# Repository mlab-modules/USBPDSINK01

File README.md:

# USBPDSINK01 - USB Power Delivery sink controller

The [MLAB](https://www.mlab.cz) module [USBPDSINK01](https://www.mlab.cz/module/USBPDSINK01) is a powerful module containing the [STUSB4500](https://www.st.com/en/interfaces-and-transceivers/stusb4500.html) [power-delivery sink controller](https://en.wikipedia.org/wiki/USB_hardware#USB_Power_Delivery). The module is designed to provide a flexible and reliable solution for various applications requiring USB power delivery PD2 and PD3 protocols. 

## Specifications

[STUSB4500](https://www.st.com/en/interfaces-and-transceivers/stusb4500.html) is a USB-C PD controller for Power Sinks / UFP (on the device side). It is certified by the USB-IF consortium for [USB Type-C](https://www.usb.org/usb-type-c) and [USB Power Delivery](https://www.usb.org/usb-charger-pd) applications (USB-C & USB PD).

### Module Features

- **USB-C Input:** The module accepts power through the USB-C connector.
- **Power Output:** The output is led to a pin header and also to a WAGO terminal block to high-power tool-free connection of powered devices.
- **Indicator Pins with LED:** Some status pins contain LEDs, and these signals are connected to the pin header.
- **Pull-up Resistors:** The module has pull-up resistors on the output signals for fast implementation into your system. PullUp voltage can be attached to header pins or can be used internal 3v3.
- **Integrated LDO:** The module is equipped with an integrated LDO for powering pullups and LED (no output).
- **External Power Supply:** The VSYS power can also be attached externally.
- **Communication via I2C:** The module communicates via I2C bus.
- **Key Features of [STUSB4500](https://www.st.com/en/interfaces-and-transceivers/stusb4500.html):**
  - Auto-run USB Type-C™ and USB PD sink controller handling and detection
  - Dead battery mode support
  - Up to 3 configurable sink PDO profiles (with permanent memory)
  - Integrated VBUS switching gates (PMOS transistor)
  - Integrated VBUS voltage monitoring
  - Internal and/or external VBUS discharge paths (for high capacitance networks)
  - Short-circuit protection on VBUS pins (22 V)
  - High-voltage capability on VBUS pins (28 V)
  - Dual power supply (VSYS and/or VDD): VDD = [4.1 V; 22 V] or VSYS = [3.0 V; 5.5 V]
  - Accessory mode support
  - Temperature range: -40 °C to 105 °C
  - ESD: 3 kV HBM - 1.5 kV CDM
  - Certified: USB Type-C™ rev 1.2, USB PD rev 2.0 (Official Test ID: TID #1000133)
  - Interoperable with USB PD rev 3.0

### Pinout and Their Meaning

- **ALERT:** Notification of various states and events.
- **USB-C orientation:** Indication of the connected side of the USB-C cable.
- **CONNECTED:** Cable connection indication.
- **GPIO:** General input/output pin, configurable for various purposes.
- **OK2 & OK3:** Pins that are active when the corresponding PDO is selected. Can indicate the selected voltage.
- **RESET:** Pin for resetting the USB-PD controller.

## Possible Applications
The MLAB module USBPDSINK01 is ideal for a wide range of applications, including:

- **Device Charging:** Fast and efficient charging of devices with high battery capacity. The module allows automatic negotiation of higher voltage from the source (>5V) up to 100W (20V@5A), ensuring the optimal charging profile for various types of batteries.

- **Scientific and Industrial Applications:** Flexible power and control for various scientific and industrial applications. With the ability to configure up to three sink PDO profiles, the module can be tailored to specific research or experiment needs.

- **Development and Testing:** The module can be used as part of development and testing stations for various products. With integrated VBUS switching gates and short-circuit protection up to 22 V, the module offers a robust and safe solution for testing and tuning.

- **Universal Power Source:** The module can serve as a universal power source for various devices, including charges, speakers, machines, or other electronic devices that require high-wattage power sources.

## Schematics

## Documentation
- [STUSB4500 Datasheet](https://www.st.com/resource/en/datasheet/stusb4500.pdf)

## Conclusion

The MLAB module USBPDSINK01 represents a robust and flexible solution for various applications requiring USB power delivery. With the integrated STUSB4500 controller, advanced features, and a wide range of possible applications, this module is the ideal choice for developers and engineers looking for a reliable and powerful solution.

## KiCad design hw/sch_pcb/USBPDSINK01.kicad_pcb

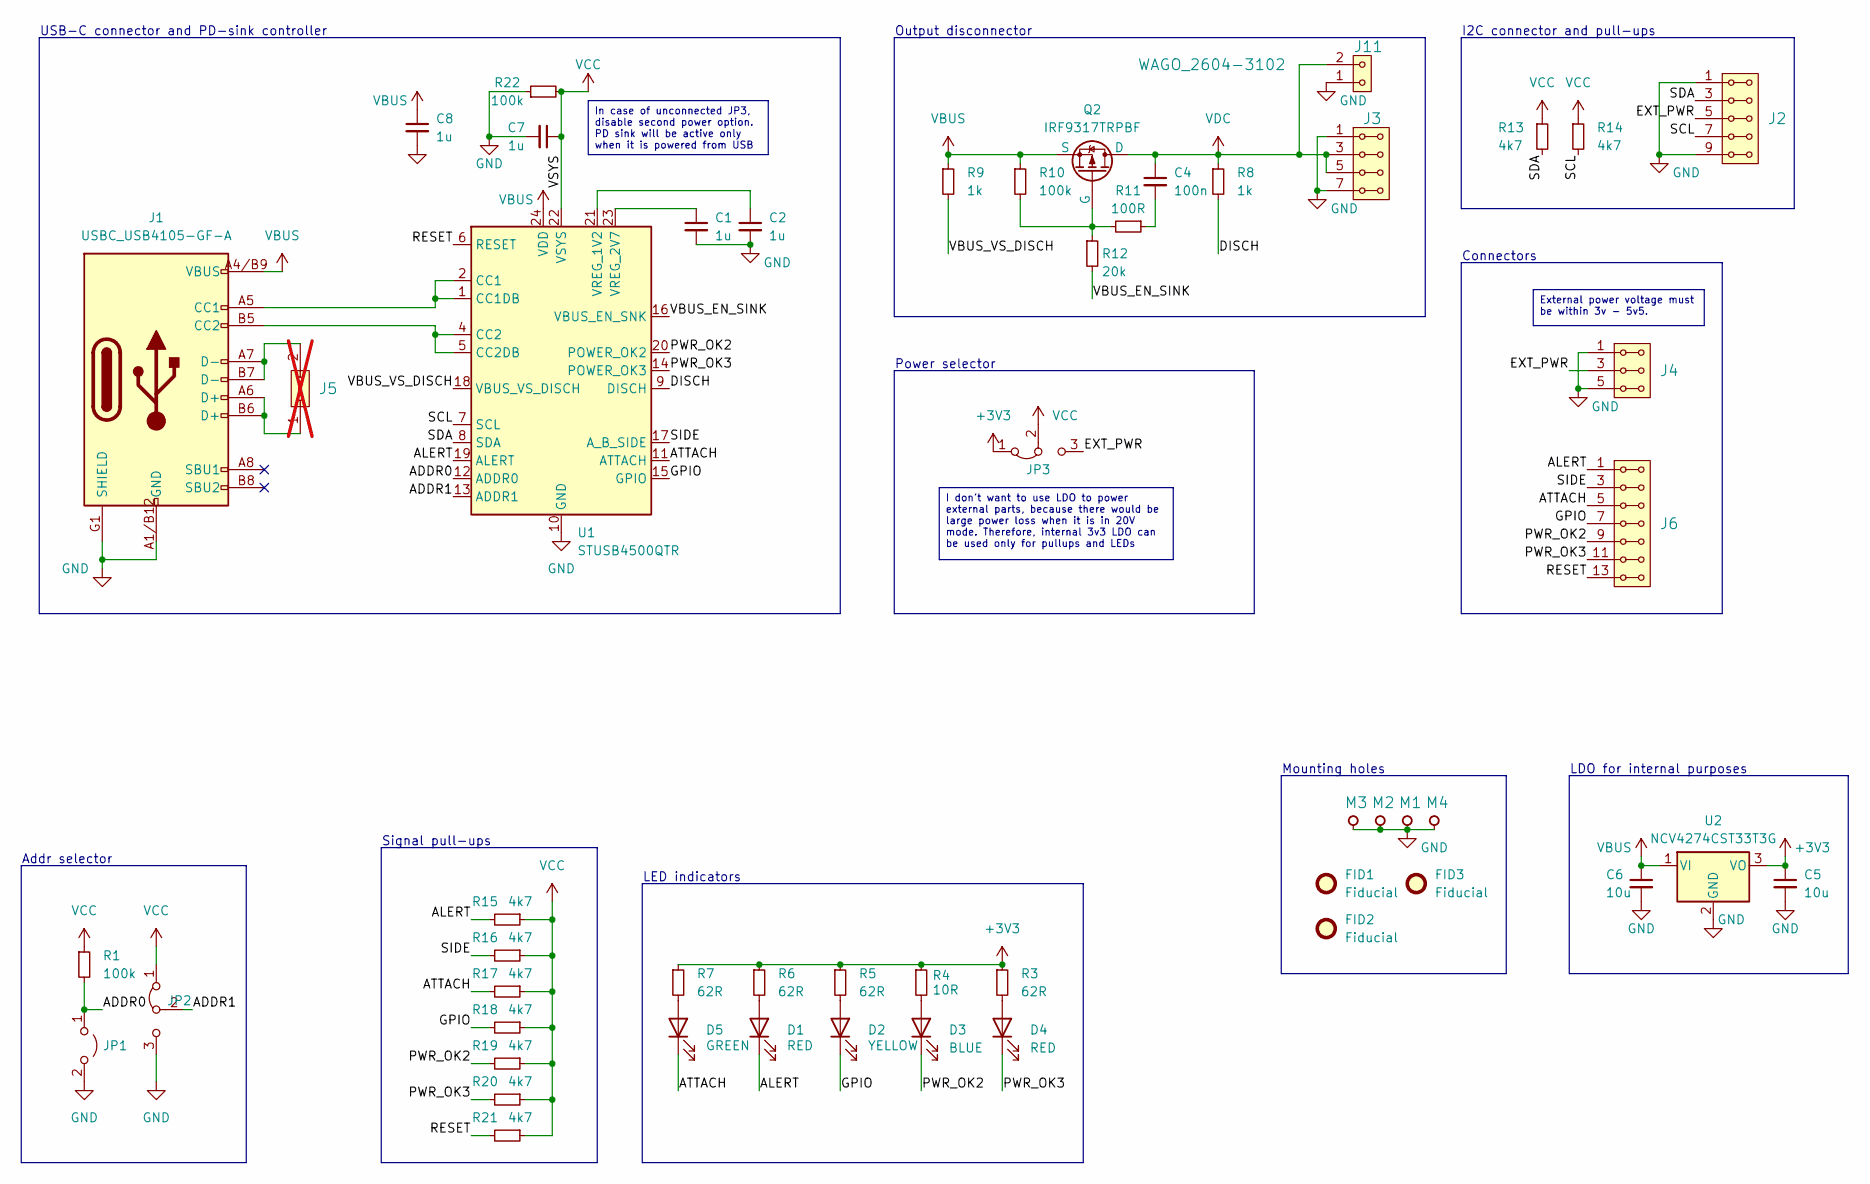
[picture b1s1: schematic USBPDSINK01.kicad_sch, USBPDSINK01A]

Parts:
C1, C2, C7, C8: 1u; C_0805_2012Metric; MPN C0805 1u
C4: 100n; C_0805_2012Metric; MPN C0805 100n
C5, C6: 10u; C_0805_2012Metric; MPN C0805 10u
D1, D4: RED; LED_1206_mill; MPN KPTR-3216SURCK
D2: YELLOW; LED_1206_mill; MPN KPTR-3216SYCK
D3: BLUE; LED_1206_mill; MPN KPTR-3216QBC-D
D5: GREEN; LED_1206_mill; MPN KPTR-3216CGCK
FID1, FID2, FID3: Fiducial; Fiducial_1mm_Mask2mm
J1: USBC_USB4105-GF-A; USBC GCT_USB4105-GF-A; MPN USB4105-GF-A
J2: HEADER_2x05_PARALLEL; PinHeader_2x05_P2.54mm_Vertical
J3: HEADER_2x04_PARALLEL; PinHeader_2x04_P2.54mm_Vertical
J4: HEADER_2x03_PARALLEL; PinHeader_2x03_P2.54mm_Vertical
J5: HEADER_2x01; PinHeader_2x01_P2.54mm_Vertical; not fitted
J6: HEADER_2x07_PARALLEL; PinHeader_2x07_P2.54mm_Vertical
J11: WAGO_2604-3102; TerminalBlock_WAGO_2604-3102_1x02_P5.00mm_Vertical; MPN 2604-3102
JP1: Jumper_2_Open; PinHeader_2x01_P2.54mm_Vertical
JP2: Jumper_3_Bridged12; SolderJumper-3_P1.3mm_Bridged12_RoundedPad1.0x1.5mm
JP3: Jumper_3_Bridged12; PinHeader_1x03_P2.54mm_Vertical
M1, M2, M3, M4: HOLE; MountingHole_3mm
Q2: IRF9317TRPBF; SOIC-8_3.9x4.9mm_P1.27mm; MPN IRF9317TRPBF
R1, R10, R22: 100k; R_0805_2012Metric; MPN R0805 100K 1%
R3, R5, R6, R7: 62R; R_0805_2012Metric; MPN R0805 62R 1%
R4: 10R; R_0805_2012Metric; MPN R0805 10R 1%
R8, R9: 1k; R_0805_2012Metric; MPN R0805 1k 1%
R11: 100R; R_0805_2012Metric; MPN R0805 100R 1%
R12: 20k; R_0805_2012Metric; MPN R0805 20k 1%
R13, R14, R15, R16, R17, R18, R19, R20, R21: 4k7; R_0805_2012Metric; MPN R0805 4k7 1%
U1: STUSB4500QTR; QFN-24-1EP_4x4mm_P0.5mm_EP2.7x2.7mm; MPN STUSB4500QTR
U2: NCV4274CST33T3G; SOT-223-3_TabPin2; MPN NCV4274CST33T3G

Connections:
+3V3: C5.1, JP3.1 (A), R3.1, R4.1, R5.1, R6.1, R7.1, U2.3 (VO)
/ADDR0: JP1.1 (A), R1.2, U1.12 (ADDR0)
/ADDR1: JP2.2 (C), U1.13 (ADDR1)
/ALERT: D1.1 (K), J6.1, J6.2, R15.2, U1.19 (ALERT)
/ATTACH: D5.1 (K), J6.5, J6.6, R17.2, U1.11 (ATTACH)
/DISCH: R8.2, U1.9 (DISCH)
/EXT_PWR: J2.5, J2.6, J4.3, J4.4, JP3.3 (B)
/GPIO: D2.1 (K), J6.7, J6.8, R18.2, U1.15 (GPIO)
/PWR_OK2: D3.1 (K), J6.9, J6.10, R19.2, U1.20 (POWER_OK2)
/PWR_OK3: D4.1 (K), J6.11, J6.12, R20.2, U1.14 (POWER_OK3)
/RESET: J6.13, J6.14, R21.2, U1.6 (RESET)
/SCL: J2.7, J2.8, R14.2, U1.7 (SCL)
/SDA: J2.3, J2.4, R13.2, U1.8 (SDA)
/SIDE: J6.3, J6.4, R16.2, U1.17 (A_B_SIDE)
/VBUS_EN_SINK: R12.2, U1.16 (VBUS_EN_SNK)
/VBUS_VS_DISCH: R9.2, U1.18 (VBUS_VS_DISCH)
GND: C1.2, C2.2, C5.2, C6.2, C7.2, C8.2, J1.A1/B12 (GND), J1.B1/A12 (GND), J1.G1 (SHIELD), J1.G2 (SHIELD), J1.G3 (SHIELD), J1.G4 (SHIELD), J2.1, J2.2, J2.9, J2.10, J3.1, J3.2, J3.7, J3.8, J4.1, J4.2, J4.5, J4.6, JP1.2 (B), JP2.3 (B), M1.1, M2.1, M3.1, M4.1, R22.1, U1.10 (GND), U1.25 (GND), U2.2 (GND); also elsewhere on the board
unnamed: C4.2, R11.1
unnamed: D1.2 (A), R6.2
unnamed: D2.2 (A), R5.2
unnamed: D3.2 (A), R4.2
unnamed: D4.2 (A), R3.2
unnamed: D5.2 (A), R7.2
unnamed: J1.A5 (CC1), U1.1 (CC1DB), U1.2 (CC1)
unnamed: J1.B5 (CC2), U1.4 (CC2), U1.5 (CC2DB)
unnamed: J1.A6 (D+), J1.B6 (D+), J5.1
unnamed: J1.A7 (D-), J1.B7 (D-), J5.2
unnamed: Q2.4 (G), R10.2, R11.2, R12.1
unnamed: C2.1, U1.21 (VREG_1V2)
unnamed: C1.1, U1.23 (VREG_2V7)
VBUS: C6.1, C8.1, J1.A4/B9 (VBUS), J1.B4/A9 (VBUS), Q2.1 (S), Q2.2 (S), Q2.3 (S), R9.1, R10.1, U1.24 (VDD), U2.1 (VI)
VCC: C7.1, JP2.1 (A), JP3.2 (C), R1.1, R13.1, R14.1, R15.1, R16.1, R17.1, R18.1, R19.1, R20.1, R21.1, R22.2, U1.22 (VSYS)
VDC: C4.1, J3.3, J3.4, J3.5, J3.6, Q2.5 (D), Q2.6 (D), Q2.7 (D), Q2.8 (D), R8.1; also elsewhere on the board

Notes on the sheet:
I don't want to use LDO to power external parts, because there would be large power loss when it is in 20V mode. Therefore, internal 3v3 LDO can be used only for pullups and LEDs
External power voltage must be within 3v - 5v5.
In case of unconnected JP3, disable second power option. PD sink will be active only when it is powered from USB
Power selector
USB-C connector and PD-sink controller
Addr selector
Mounting holes
I2C connector and pull-ups
Signal pull-ups
Connectors
LED indicators
LDO for internal purposes
Output disconnector

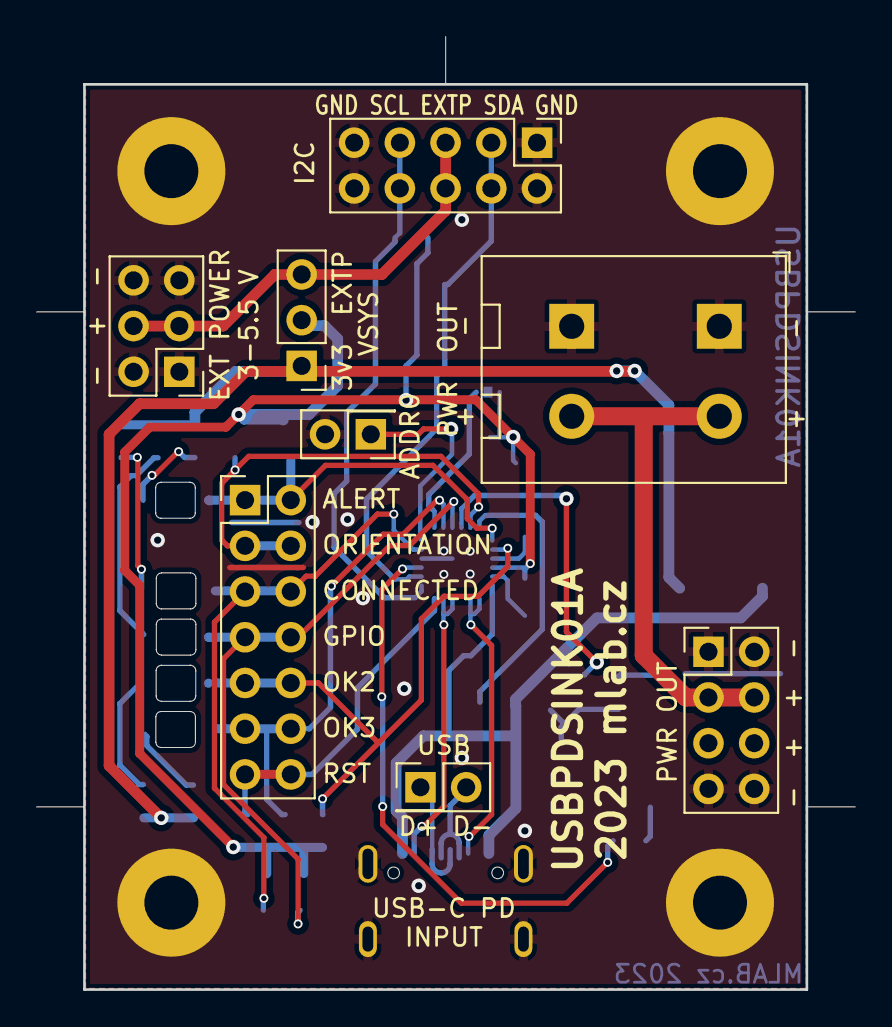
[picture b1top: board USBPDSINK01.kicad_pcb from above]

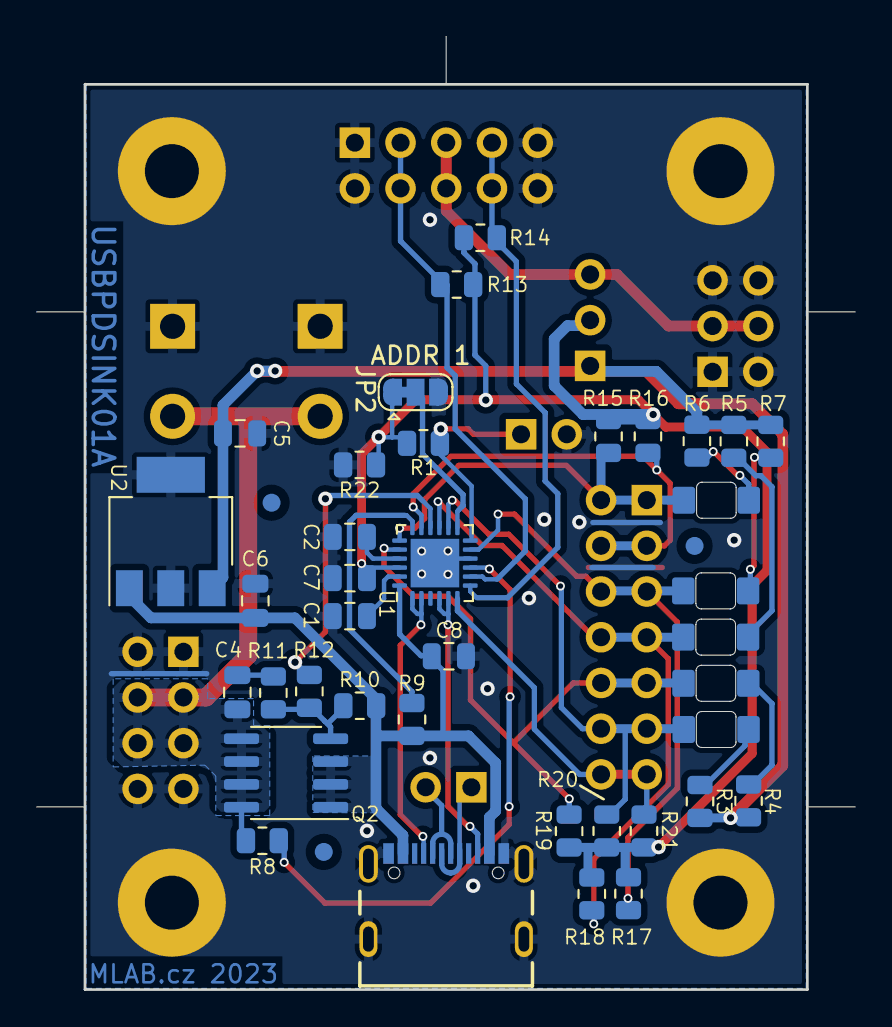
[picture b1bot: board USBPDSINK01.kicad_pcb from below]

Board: 2 copper layers, 45.4 x 52.9 mm, 53 parts (41 on the bottom side), 33 nets.

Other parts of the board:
J7: WAGO_2604-3102; TerminalBlock_WAGO_2604-3102_1x02_P5.00mm_Vertical

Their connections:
GND: J7.1; also elsewhere on the board
VDC: J7.2; also elsewhere on the board

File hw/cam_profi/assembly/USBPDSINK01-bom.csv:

Component,Description,Part,References,Value,Footprint,Quantity Per PCB,Datasheet,mfpn,mpn,ust_id,sim.pins,sim.type
1,"Unpolarized capacitor, small symbol",C_Small,C4,100n,C_0805_2012Metric,1,~,C0805 100n,C0805 100n,5c70984712875079b91f8b4c,,
2,"Unpolarized capacitor, small symbol",C_Small,C1C2C7C8,1u,C_0805_2012Metric,4,~,C0805 1u,C0805 1u,5c70984712875079b91f8b50,,
3,"Unpolarized capacitor, small symbol",C_Small,C5C6,10u,C_0805_2012Metric,2,~,C0805 10u,C0805 10u,5c70984712875079b91f8b53,,
4,Light emitting diode,LED,D3,BLUE,LED_1206_mill,1,~,KPTR-3216QBC-D,KPTR-3216QBC-D,650b4b9e462c6d9e7205459d,,
5,Light emitting diode,LED,D5,GREEN,LED_1206_mill,1,~,KPTR-3216CGCK,KPTR-3216CGCK,64ab2ec176c82a1d3b57875b,,
6,Light emitting diode,LED,D1D4,RED,LED_1206_mill,2,~,KPTR-3216SURCK,KPTR-3216SURCK,64ab2fba76c82a1d3b57877d,,
7,Light emitting diode,LED,D2,YELLOW,LED_1206_mill,1,~,KPTR-3216SYCK,KPTR-3216SYCK,650b4b13462c6d9e7205456a,,
8,"2x03 2.54 mm pitch header, 2 pins next to each other are connected",HEADER_2x03_PARALLEL,J4,HEADER_2x03_PARALLEL,PinHeader_2x03_P2.54mm_Vertical,1,,,,,,
9,"2x04 2.54 mm pitch header, 2 pins next to each other are connected",HEADER_2x04_PARALLEL,J3,HEADER_2x04_PARALLEL,PinHeader_2x04_P2.54mm_Vertical,1,,,,,,
10,"2x05 2.54 mm pitch header, 2 pins next to each other are connected",HEADER_2x05_PARALLEL,J2,HEADER_2x05_PARALLEL,PinHeader_2x05_P2.54mm_Vertical,1,,,,,,
11,"2x07 2.54 mm pitch header, 2 pins next to each other are connected",HEADER_2x07_PARALLEL,J6,HEADER_2x07_PARALLEL,PinHeader_2x07_P2.54mm_Vertical,1,,,,,,
12,USB 2.0-only Type-C Receptacle connector,USBC_USB4105-GF-A,J1,USBC_USB4105-GF-A,USBC GCT_USB4105-GF-A,1,,USB4105-GF-A,USB4105-GF-A,5fa0f94612875025b397795e,,
13,1x02 2.54 mm pitch header,HEADER_1x02,J7,WAGO_2604-3102,TerminalBlock_WAGO_2604-3102_1x02_P5.00mm_Vertical,1,,2604-3102,2604-3102,,,
14,"Jumper, 2-pole, open",Jumper_2_Open,JP1,Jumper_2_Open,PinHeader_2x01_P2.54mm_Vertical,1,~,,,,,
15,"Jumper, 3-pole, pins 1+2 closed/bridged",Jumper_3_Bridged12,JP2,Jumper_3_Bridged12,SolderJumper-3_P1.3mm_Bridged12_RoundedPad1.0x1.5mm,1,~,,,,,
16,"Jumper, 3-pole, pins 1+2 closed/bridged",Jumper_3_Bridged12,JP3,Jumper_3_Bridged12,PinHeader_1x03_P2.54mm_Vertical,1,~,,,,,
17,"P-MOSFET transistor, drain/source/gate, 40V, 9A, 12mOhm",IRF7469PbF,Q2,IRF9317TRPBF,SOIC-8_3.9x4.9mm_P1.27mm,1,,IRF9317TRPBF,IRF9317TRPBF,64f8de80f3b9d36f37fc9304,1=D 2=G 3=S,VDMOS
18,"Resistor, small symbol",R_Small,R4,10R,R_0805_2012Metric,1,~,R0805 10R 1%,R0805 10R 1%,5c70984512875079b91f896d,,
19,"Resistor, small symbol",R_Small,R3R5R6R7,62R,R_0805_2012Metric,4,~,R0805 62R 1%,R0805 62R 1%,5c70984512875079b91f8974,,
20,"Resistor, small symbol",R_Small,R11,100R,R_0805_2012Metric,1,~,R0805 100R 1%,R0805 100R 1%,5c70984512875079b91f8977,,
21,"Resistor, small symbol",R_Small,R8R9,1k,R_0805_2012Metric,2,~,R0805 1k 1%,R0805 1k 1%,5c70984512875079b91f898c,,
22,"Resistor, small symbol",R_Small,R13R14R15R16R17R18R19R20R21,4k7,R_0805_2012Metric,9,~,R0805 4k7 1%,R0805 4k7 1%,5c70984612875079b91f8995,,
23,"Resistor, small symbol",R_Small,R12,20k,R_0805_2012Metric,1,~,R0805 20k 1%,R0805 20k 1%,5c70984612875079b91f89a3,,
24,"Resistor, small symbol",R_Small,R1R10R22,100k,R_0805_2012Metric,3,~,R0805 100K 1%,R0805 100K 1%,639ed3d540d28a66c9e88a9e,,
25,"50mA Ultra-Low Quiescent Current LDO Voltage Regulator, 3.3V fixed output, TO-252/SOT-223",LM2936-3.3,U2,NCV4274CST33T3G,SOT-223-3_TabPin2,1,https://cz.mouser.com/datasheet/2/308/1/NCV4274C_D-2317600.pdf,NCV4274CST33T3G,NCV4274CST33T3G,650b45d7462c6d9e720544df,,
26,"Stand-alone USB PD controller (with sink Auto-run mode), QFN-24",STUSB4500QTR,U1,STUSB4500QTR,QFN-24-1EP_4x4mm_P0.5mm_EP2.7x2.7mm,1,https://www.st.com/resource/en/datasheet/stusb4500.pdf,STUSB4500QTR,STUSB4500QTR,64f8daa2f3b9d36f37fc92aa,,

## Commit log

2023-08-22 initial commit of USBPDSINK01
2023-08-23 Navrh schema
2023-08-23 Update metadata files
2023-08-23 Update actions products
2023-08-23 update improvements in schematics and layout
2023-08-23 update component values
2023-08-23 solve DRC
2023-08-23 silkscreen
2023-08-23 update wago connector
2023-08-23 add render
2023-08-23 set sheet template
2023-09-06 minor updates in layout, clean schematics, add components MFPN
2023-09-06 version uploaded to aisler
2023-09-07 Update README.md
    Cleanup the structure.
2023-09-07 Update title block.
2023-09-07 Cleanup traces.
2023-09-11 Update workflow files
2023-09-16 Update status
2023-09-17 automated commit; add github actions
2023-09-20 add ustid, change LDO
2023-09-22 Kontrola a priprava PCB na vyrobu
2023-09-24 Kontrola, upravi pred vyrobou
2023-10-04 Edit B.Fab
2023-10-13 Solve some issues form 01A
